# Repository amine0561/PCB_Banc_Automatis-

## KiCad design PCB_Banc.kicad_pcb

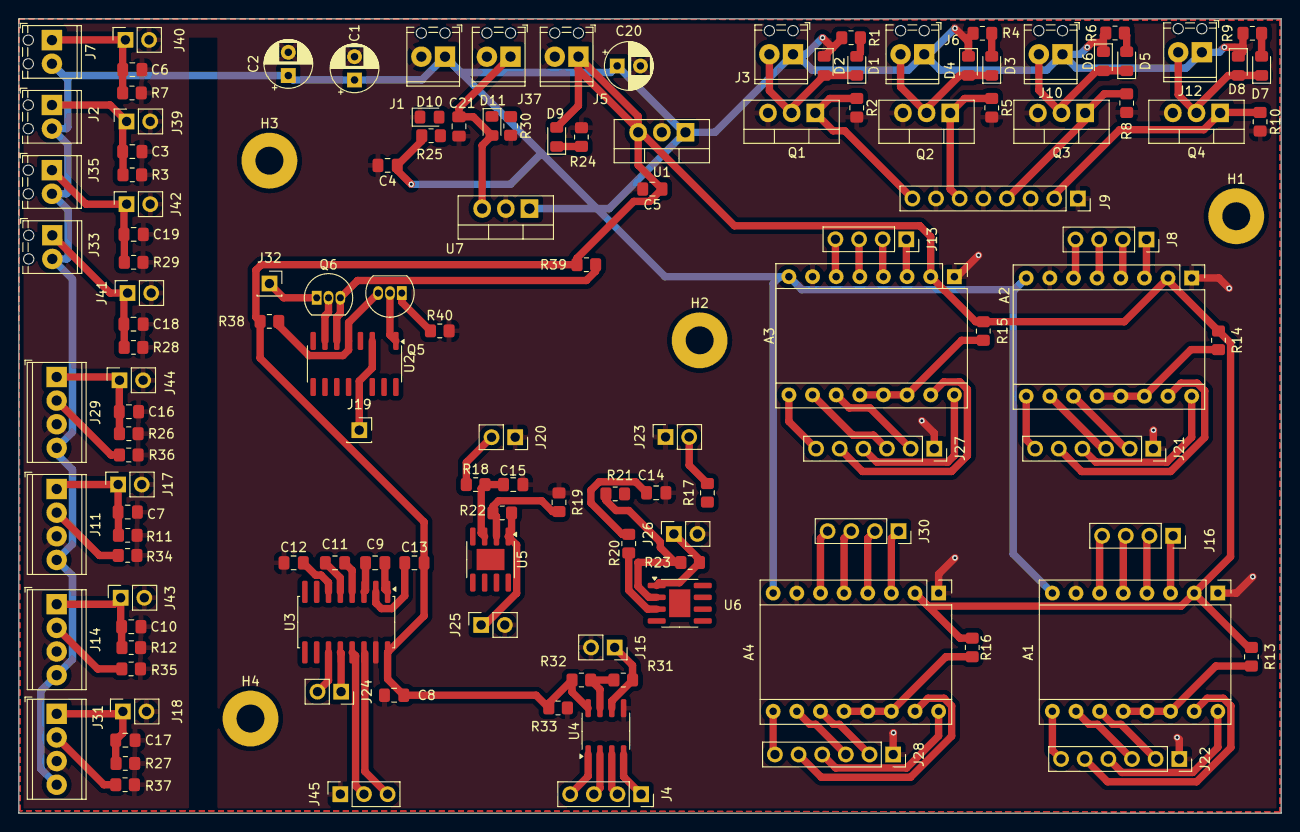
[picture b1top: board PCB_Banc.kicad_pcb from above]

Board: 2 copper layers, 135.6 x 85.3 mm, 135 parts (0 on the bottom side), 103 nets.

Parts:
A1, A2, A3, A4: Pololu_Breakout_A4988; Pololu_Breakout-16_15.2x20.3mm
C1, C20: 0.33µF; CP_Radial_D5.0mm_P2.50mm
C2: 470µ; CP_Radial_D5.0mm_P2.50mm
C3, C6, C7, C10, C16, C17, C18, C19: 470n; C_0805_2012Metric_Pad1.18x1.45mm_HandSolder
C4: 100n; C_0805_2012Metric_Pad1.18x1.45mm_HandSolder
C5, C21: 0.1µ; C_0805_2012Metric_Pad1.18x1.45mm_HandSolder
C8, C9, C11, C12, C13: 1µF; C_0805_2012Metric_Pad1.18x1.45mm_HandSolder
C14: 2.2µF; C_0805_2012Metric_Pad1.18x1.45mm_HandSolder
C15: 100nF; C_0805_2012Metric_Pad1.18x1.45mm_HandSolder
D1, D3, D5, D7, D9, D10, D11: LED; LED_0805_2012Metric_Pad1.15x1.40mm_HandSolder
D2, D4, D6, D8: 1N4001; D_0805_2012Metric_Pad1.15x1.40mm_HandSolder
H1, H2, H3, H4: MountingHole; MountingHole_3mm_Pad
J1, J2, J3, J6, J7, J10, J12, J33, J35: Screw_Terminal_01x02; TerminalBlock_Phoenix_MPT-0,5-2-2.54_1x02_P2.54mm_Horizontal
J4, J8, J13, J16, J30: Conn_01x04; PinSocket_1x04_P2.54mm_Vertical
J5: Arduino pwr supply; TerminalBlock_Phoenix_MPT-0,5-2-2.54_1x02_P2.54mm_Horizontal
J9: Conn_01x08; PinSocket_1x08_P2.54mm_Vertical
J11, J14, J29, J31: Screw_Terminal_01x04; TerminalBlock_Phoenix_MPT-0,5-4-2.54_1x04_P2.54mm_Horizontal
J15, J17, J18, J20, J23, J24, J25, J26, J39, J40, J41, J42, J43, J44: Conn_01x02; PinSocket_1x02_P2.54mm_Vertical
J19, J32: Conn_01x01; PinSocket_1x01_P2.54mm_Vertical
J21, J22, J27, J28: Conn_01x06; PinSocket_1x06_P2.54mm_Vertical
J37: TerminalBlock_Phoenix_MPT-0,5-2-2.54_1x02_P2.54mm_Horizontal
J45: Conn_01x03; PinSocket_1x03_P2.54mm_Vertical
Q1, Q2, Q3, Q4: IRLZ44N; TO-220-3_Vertical
Q5, Q6: 2N3904; TO-92_Inline
R1, R4, R6, R9: 130; R_0805_2012Metric_Pad1.20x1.40mm_HandSolder
R2, R5, R8, R10: 10K; R_0805_2012Metric_Pad1.20x1.40mm_HandSolder
R3, R7, R28, R29, R32, R33: 1k; R_0805_2012Metric_Pad1.20x1.40mm_HandSolder
R11, R12, R26, R27, R34, R35, R36, R37: 1K; R_0805_2012Metric_Pad1.20x1.40mm_HandSolder
R13, R14, R15, R16, R18, R19, R20, R21, R22, R23: 5k; R_0805_2012Metric_Pad1.20x1.40mm_HandSolder
R17: 200; R_0805_2012Metric_Pad1.20x1.40mm_HandSolder
R24, R30: 470; R_0805_2012Metric_Pad1.20x1.40mm_HandSolder
R25: 2k; R_0805_2012Metric_Pad1.20x1.40mm_HandSolder
R31: 120; R_0805_2012Metric_Pad1.20x1.40mm_HandSolder
R38: 330; R_0805_2012Metric_Pad1.20x1.40mm_HandSolder
R39: 100; R_0805_2012Metric_Pad1.20x1.40mm_HandSolder
R40: 499; R_0805_2012Metric_Pad1.20x1.40mm_HandSolder
U1: L7805; TO-220-3_Vertical
U2: LM324; SOIC-14-16_3.9x9.9mm_P1.27mm
U3: MAX232; SOIC-16W_5.3x10.2mm_P1.27mm
U4: MAX1487E; SOIC-8_3.9x4.9mm_P1.27mm
U5, U6: LM358; SOIC-8-1EP_3.9x4.9mm_P1.27mm_EP2.29x3mm
U7: LM7812_TO220; TO-220-3_Vertical

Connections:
+5V: A1.2 (VDD), A2.2 (VDD), A3.2 (VDD), A4.2 (VDD), C5.1, C8.1, C13.2, D9.2 (A), J5.1, R13.2, R14.2, R15.2, R16.2, R32.2, R33.1, R38.1, R39.1, U1.3 (OUT), U3.16 (VCC), U4.8 (VCC)
+12V: C21.1, D11.2 (A), J37.1, U7.3 (VO)
+24V: A1.8 (VMOT), A2.8 (VMOT), A3.8 (VMOT), A4.8 (VMOT), C1.1, C2.1, C4.1, C20.1, D2.1 (K), D4.1 (K), D6.1 (K), D8.1 (K), J1.1, J2.2, J3.1, J6.1, J7.2, J10.1, J11.4, J12.1, J14.4, J29.4, J31.4, J33.2, J35.2, R1.1, R4.1, R6.1, R9.1, R25.1, U1.1 (IN), U7.1 (VI)
GND: A1.1 (GND), A1.7 (GND), A2.1 (GND), A2.7 (GND), A3.1 (GND), A3.7 (GND), A4.1 (GND), A4.7 (GND), C1.2, C2.2, C3.2, C4.2, C5.2, C6.2, C7.2, C8.2, C10.2, C12.1, C14.2, C15.1, C16.2, C17.2, C18.2, C19.2, C20.2, C21.2, D10.1 (K), J1.2, J5.2, J9.1, J9.3, J9.5, J9.7, J11.3, J14.3, J15.2, J17.2, J18.2, J20.1, J21.1, J22.1, J23.1, J25.2, J26.2, J27.1, J28.1, J29.3, J31.3, J37.2, J39.2, J40.2, J41.2, J42.2, J43.2, J44.2, J45.1, Q1.3 (S), Q2.3 (S), Q3.3 (S), Q4.3 (S), R2.2, R3.1, R5.2, R7.1, R8.2, R10.2, R11.1, R12.1, R19.2, R21.2, R24.2, R26.1, R27.1, R28.1, R29.1, R30.2, R33.2, R34.1, R35.1, R36.1, R37.1, R40.2, U1.2 (GND), U3.15 (GND), U4.5 (GND), U7.2 (GND)
unnamed: A1.4 (1A), J16.2
unnamed: A1.3 (1B), J16.1
unnamed: A1.5 (2A), J16.3
unnamed: A1.6 (2B), J16.4
unnamed: A1.16 (DIR), J22.4
unnamed: A1.10 (MS1), J22.3
unnamed: A1.11 (MS2), J22.2
unnamed: A1.12 (MS3), A1.13 (~RESET), A1.14 (~SLEEP), R13.1
unnamed: A1.15 (STEP), J22.5
unnamed: A1.9 (~ENABLE), J22.6
unnamed: A2.4 (1A), J8.2
unnamed: A2.3 (1B), J8.1
unnamed: A2.5 (2A), J8.3
unnamed: A2.6 (2B), J8.4
unnamed: A2.16 (DIR), J21.4
unnamed: A2.10 (MS1), J21.3
unnamed: A2.11 (MS2), J21.2
unnamed: A2.12 (MS3), A2.13 (~RESET), A2.14 (~SLEEP), R14.1
unnamed: A2.15 (STEP), J21.5
unnamed: A2.9 (~ENABLE), J21.6
unnamed: A3.4 (1A), J13.2
unnamed: A3.3 (1B), J13.1
unnamed: A3.5 (2A), J13.3
unnamed: A3.6 (2B), J13.4
unnamed: A3.16 (DIR), J27.4
unnamed: A3.10 (MS1), J27.3
unnamed: A3.11 (MS2), J27.2
unnamed: A3.12 (MS3), A3.13 (~RESET), A3.14 (~SLEEP), R15.1
unnamed: A3.15 (STEP), J27.5
unnamed: A3.9 (~ENABLE), J27.6
unnamed: A4.4 (1A), J30.2
unnamed: A4.3 (1B), J30.1
unnamed: A4.5 (2A), J30.3
unnamed: A4.6 (2B), J30.4
unnamed: A4.16 (DIR), J28.4
unnamed: A4.10 (MS1), J28.3
unnamed: A4.11 (MS2), J28.2
unnamed: A4.12 (MS3), A4.13 (~RESET), A4.14 (~SLEEP), R16.1
unnamed: A4.15 (STEP), J28.5
unnamed: A4.9 (~ENABLE), J28.6
unnamed: C14.1, R17.2, R20.1
unnamed: D1.2 (A), R1.2
unnamed: D1.1 (K), D2.2 (A), J3.2, Q1.2 (D)
unnamed: D3.2 (A), R4.2
unnamed: D3.1 (K), D4.2 (A), J6.2, Q2.2 (D)
unnamed: D5.2 (A), R6.2
unnamed: D5.1 (K), D6.2 (A), J10.2, Q3.2 (D)
unnamed: D7.2 (A), R9.2
unnamed: D7.1 (K), D8.2 (A), J12.2, Q4.2 (D)
unnamed: D9.1 (K), R24.1
unnamed: D10.2 (A), R25.2
unnamed: D11.1 (K), R30.1
unnamed: C3.1, J2.1, J39.1, R3.2
unnamed: J4.1, U4.4 (DI)
unnamed: J4.2, U4.3 (DE)
unnamed: J4.3, U4.2 (~RE)
unnamed: J4.4, U4.1 (RO)
unnamed: J9.2, Q4.1 (G), R10.1
unnamed: J9.4, Q3.1 (G), R8.1
unnamed: J9.6, Q2.1 (G), R5.1
unnamed: J9.8, Q1.1 (G), R2.1
unnamed: C7.1, J11.1, J17.1, R11.2
unnamed: J11.2, R34.2
unnamed: C10.1, J14.1, J43.1, R12.2
unnamed: J14.2, R35.2
unnamed: J15.1, R31.2, U4.6 (A)
unnamed: C17.1, J18.1, J31.1, R27.2
unnamed: J19.1, U2.3 (+)
unnamed: J20.2, R18.1
unnamed: J23.2, R17.1
unnamed: J24.1, U3.12 (R1OUT)
unnamed: J24.2, U3.11 (T1IN)
unnamed: J25.1, R22.2, U5.1
unnamed: J26.1, R23.2, U6.1
unnamed: C16.1, J29.1, J44.1, R26.2
unnamed: J29.2, R36.2
unnamed: J31.2, R37.2
unnamed: J32.1, Q6.1 (E)
unnamed: C18.1, J33.1, J41.1, R28.2
unnamed: C19.1, J35.1, J42.1, R29.2
unnamed: C6.1, J7.1, J40.1, R7.2
unnamed: J45.2, U3.13 (R1IN)
unnamed: J45.3, U3.14 (T1OUT)
unnamed: Q5.2 (B), U2.1
unnamed: Q5.3 (C), R38.2, U2.5 (+)
unnamed: Q5.1 (E), R40.1
unnamed: Q6.2 (B), U2.7
unnamed: Q6.3 (C), R39.2, U2.6 (-)
unnamed: C9.1, U3.1 (C1+)
unnamed: C9.2, U3.3 (C1-)
unnamed: C11.1, U3.4 (C2+)
unnamed: C11.2, U3.5 (C2-)
unnamed: C13.1, U3.2 (VS+)
unnamed: C12.2, U3.6 (VS-)
unnamed: R31.1, R32.1, U4.7 (B)
unnamed: C15.2, R18.2, U5.3 (+)
unnamed: R19.1, R22.1, U5.2 (-)
unnamed: R20.2, U6.3 (+)
unnamed: R21.1, R23.1, U6.2 (-)

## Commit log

2024-06-26 alim
2024-07-02 before edit
2024-07-04 next step
2024-07-04 before rs485
2024-07-08 soon all done
2024-07-09 saving
2024-09-20 PCB valid prod
